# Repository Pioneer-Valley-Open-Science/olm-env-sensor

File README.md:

olm-env-sensor
==============

Peripheral for OLM, measuring ambient temperature and humidity with thermistor probe.

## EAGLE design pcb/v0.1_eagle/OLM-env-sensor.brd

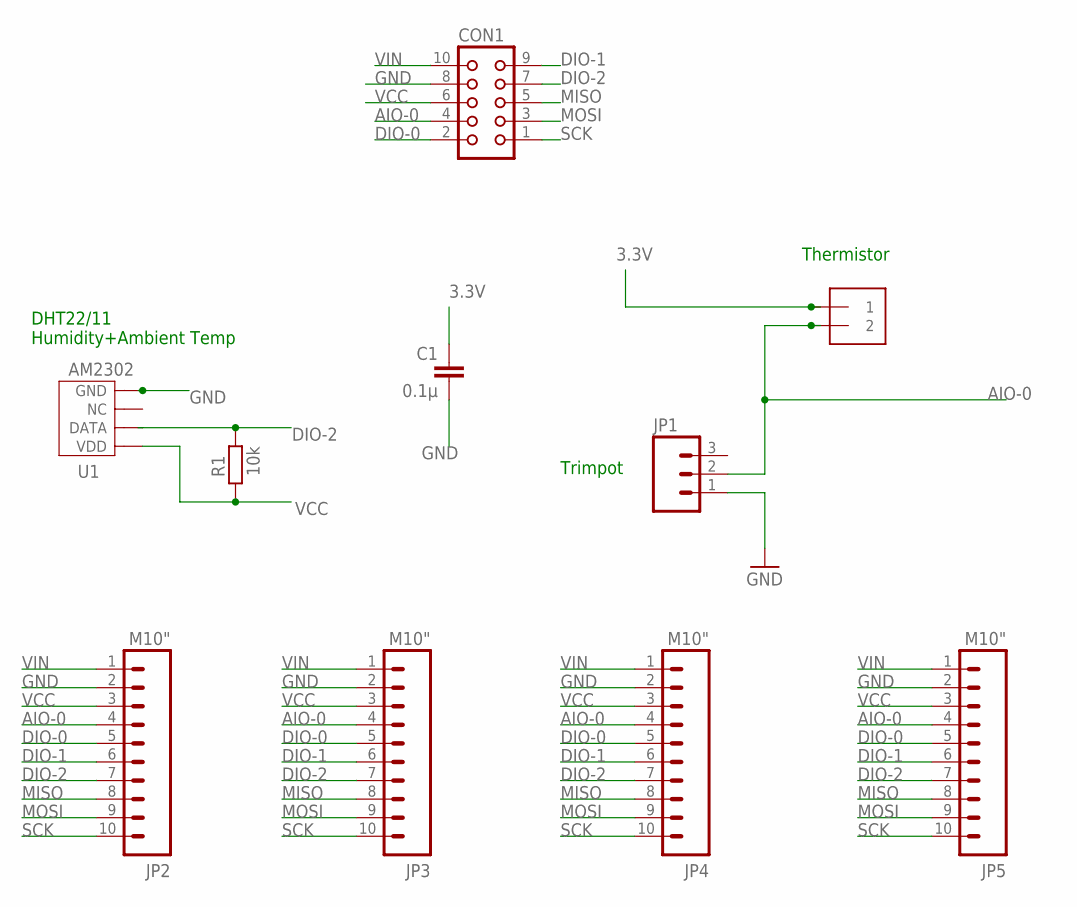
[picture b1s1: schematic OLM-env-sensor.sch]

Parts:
C1: 0.1µ; C025-024X044
CON1: CON10L
J1: 1X2-3.5MM
JP1: M03PTH; 1X03
JP2, JP3, JP4, JP5: M10"; 1X10
R1: 10k; 0204/7
U1: AM2302

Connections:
3.3V: C1.1, J1.1
AIO-0: CON1.4, J1.2, JP1.2, JP2.4, JP3.4, JP4.4, JP5.4
DIO-0: CON1.2, JP2.5, JP3.5, JP4.5, JP5.5
DIO-1: CON1.9, JP2.6, JP3.6, JP4.6, JP5.6
DIO-2: CON1.7, JP2.7, JP3.7, JP4.7, JP5.7, R1.2, U1.P$2 (DATA)
GND: C1.2, CON1.8, JP1.1, JP2.2, JP3.2, JP4.2, JP5.2, U1.P$4 (GND)
MISO: CON1.5, JP2.8, JP3.8, JP4.8, JP5.8
MOSI: CON1.3, JP2.9, JP3.9, JP4.9, JP5.9
SCK: CON1.1, JP2.10, JP3.10, JP4.10, JP5.10
VCC: CON1.6, JP2.3, JP3.3, JP4.3, JP5.3, R1.1, U1.P$1 (VDD)
VIN: CON1.10, JP2.1, JP3.1, JP4.1, JP5.1

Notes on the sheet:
Thermistor
DHT22/11 Humidity+Ambient Temp
Trimpot

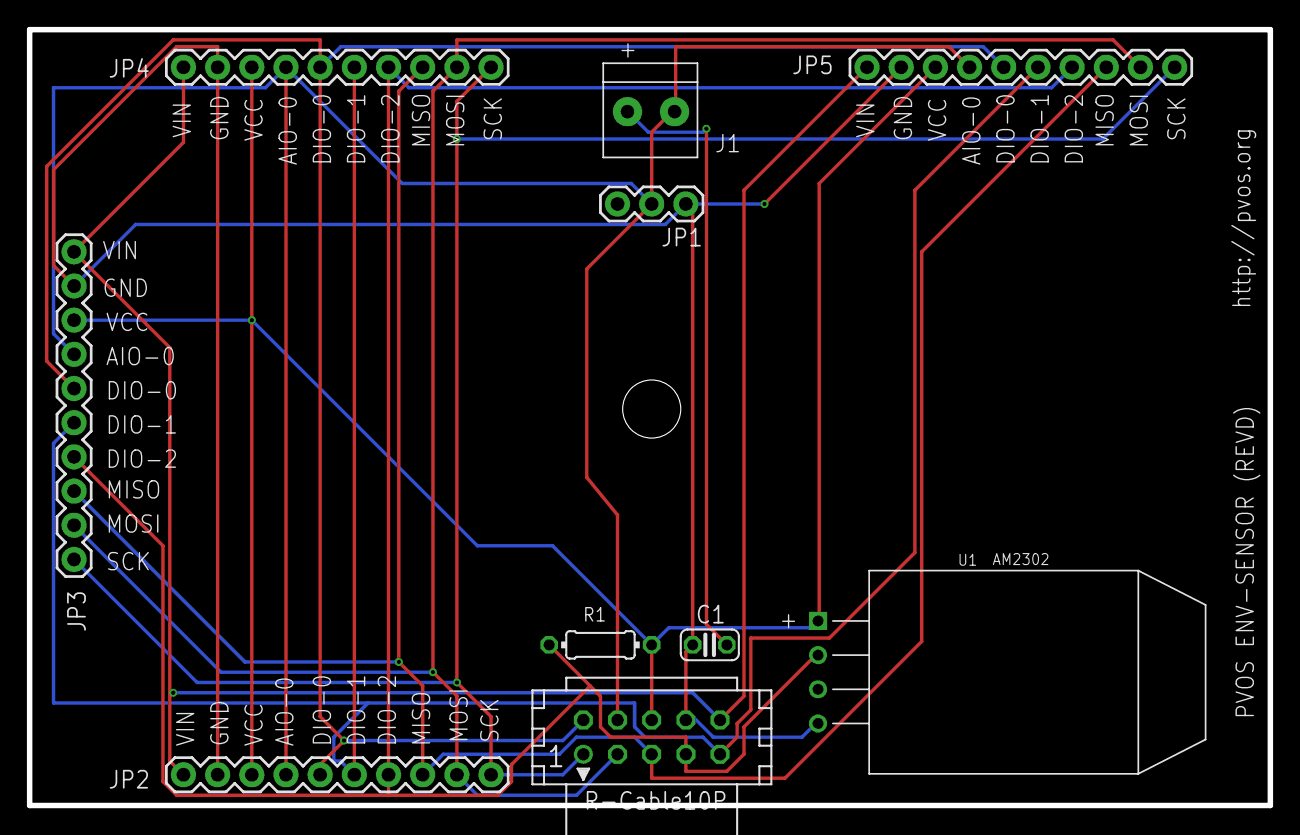
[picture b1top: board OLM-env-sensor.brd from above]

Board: 2 copper layers, 92.2 x 57.7 mm, 10 parts (0 on the bottom side), 11 nets.

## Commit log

2013-07-07 basic components in schematic, not wired yet
2013-07-07 fixed wiring
2013-07-07 use 'make clean' to remove trashy files
2013-07-07 fixed bug that would accidently erase source files
2013-07-07 PDF print out

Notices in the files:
parts and their libraries:
SparkFun-Connectors: Licensing: CC v3.0 Share-Alike You are welcome to use this library for commercial purposes.
